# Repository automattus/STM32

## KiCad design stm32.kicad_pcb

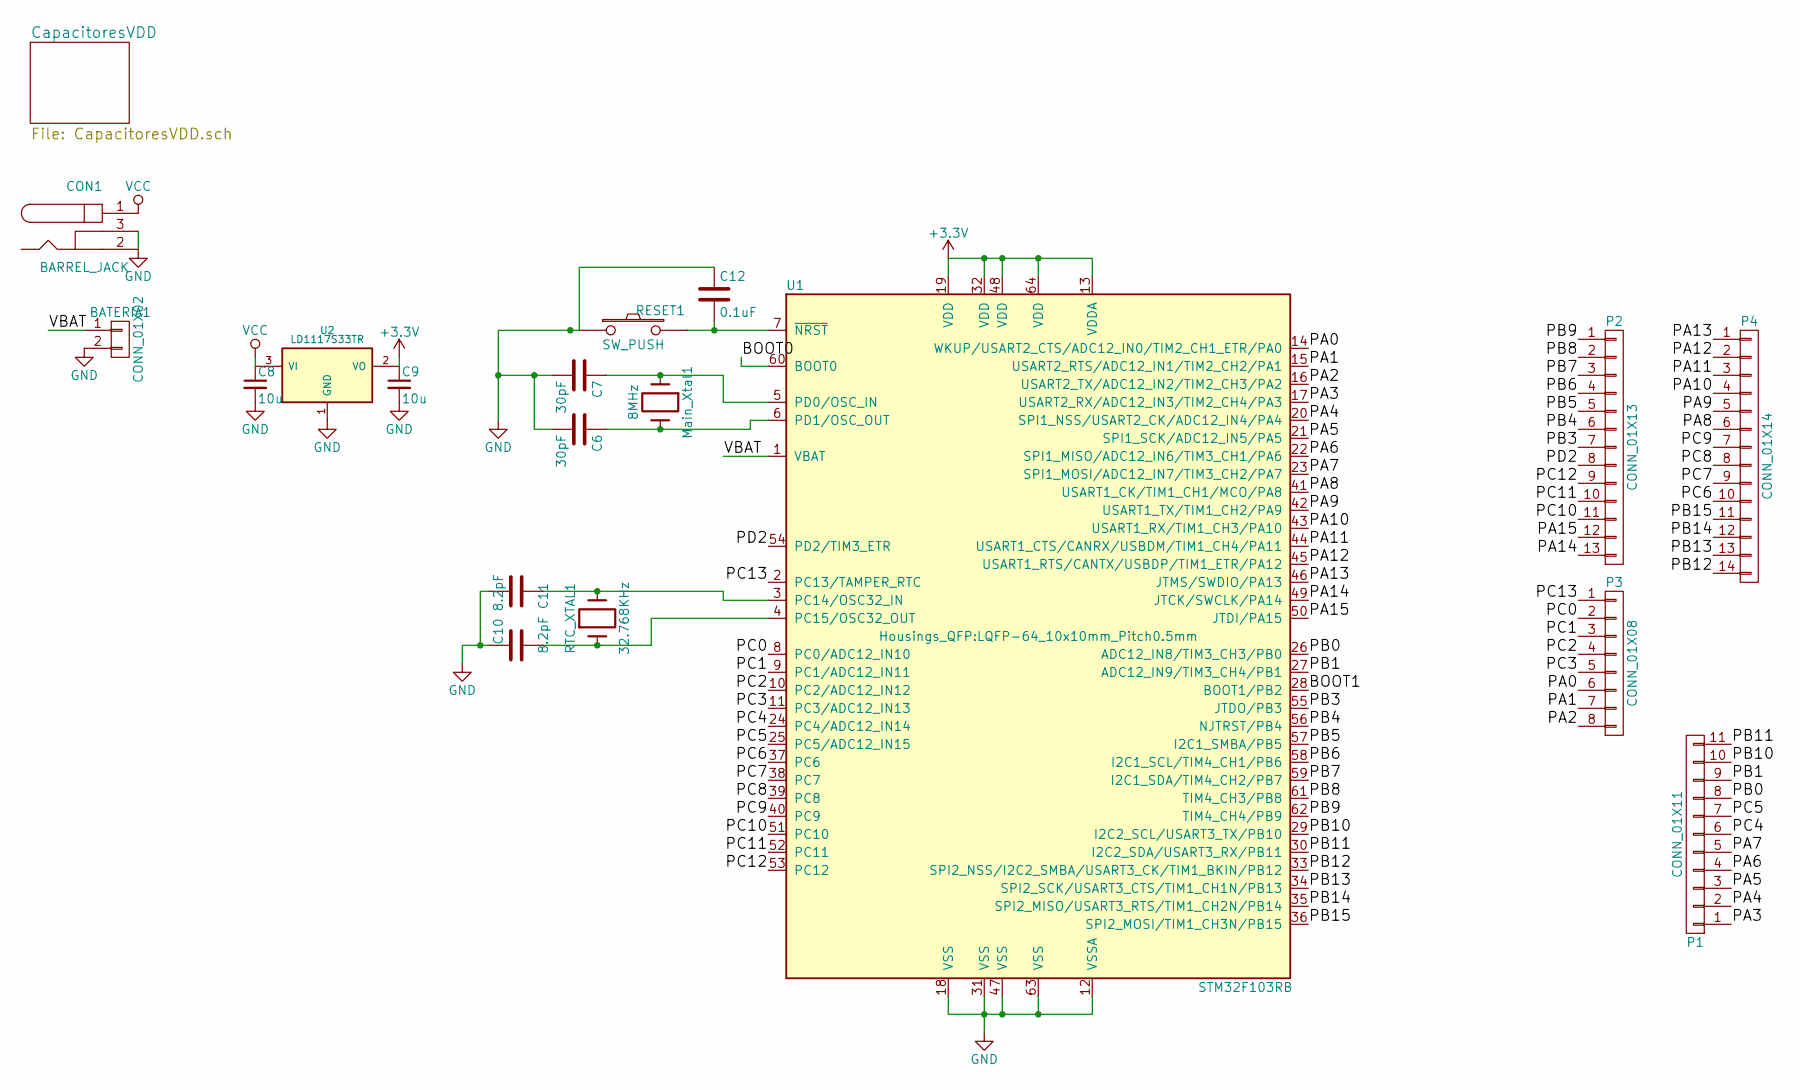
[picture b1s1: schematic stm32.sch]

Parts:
BATERIA1: CONN_01X02; bornier2
C6, C7: 30pF; C_0603_HandSoldering
C8, C9: 10u; C_0603_HandSoldering
C10, C11: 8.2pF; C_0603_HandSoldering
C12: 0.1uF; C_0603_HandSoldering
CON1: BARREL_JACK
Main_Xtal1: 8MHz; HC-18UV
P1: CONN_01X11; Pin_Header_Straight_1x11
P2: CONN_01X13; Pin_Header_Straight_1x13
P3: CONN_01X08; Pin_Header_Straight_1x08
P4: CONN_01X14; Pin_Header_Straight_1x14
RESET1: SW_PUSH; SW_PUSH_SMALL
RTC_XTAL1: 32.768KHz; Crystal_Round_Vertical_3mm
U1: STM32F103RB; LQFP-64_10x10mm_Pitch0.5mm
U2: LD1117S33TR; SOT-223

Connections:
+3V3: C9.1, U1.13 (VDDA), U1.19 (VDD), U1.32 (VDD), U1.48 (VDD), U1.64 (VDD), U2.2 (VO); also elsewhere on the board
/PA0: P3.6, U1.14 (WKUP/USART2_CTS/ADC12_IN0/TIM2_CH1_ETR/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)
/PA1: P3.7, U1.15 (USART2_RTS/ADC12_IN1/TIM2_CH2/PA1)
/PA2: P3.8, U1.16 (USART2_TX/ADC12_IN2/TIM2_CH3/PA2)
/PA3: P1.1, U1.17 (USART2_RX/ADC12_IN3/TIM2_CH4/PA3)
/PA4: P1.2, U1.20 (SPI1_NSS/USART2_CK/ADC12_IN4/PA4)
/PA5: P1.3, U1.21 (SPI1_SCK/ADC12_IN5/PA5)
/PA6: P1.4, U1.22 (SPI1_MISO/ADC12_IN6/TIM3_CH1/PA6)
/PA7: P1.5, U1.23 (SPI1_MOSI/ADC12_IN7/TIM3_CH2/PA7)
/PA8: P4.6, U1.41 (USART1_CK/TIM1_CH1/MCO/PA8)
/PA9: P4.5, U1.42 (USART1_TX/TIM1_CH2/PA9)
/PA10: P4.4, U1.43 (USART1_RX/TIM1_CH3/PA10)
/PA11: P4.3, U1.44 (USART1_CTS/CANRX/USBDM/TIM1_CH4/PA11)
/PA12: P4.2, U1.45 (USART1_RTS/CANTX/USBDP/TIM1_ETR/PA12)
/PA13: P4.1, U1.46 (JTMS/SWDIO/PA13)
/PA14: P2.13, U1.49 (JTCK/SWCLK/PA14)
/PA15: P2.12, U1.50 (JTDI/PA15)
/PB0: P1.8, U1.26 (ADC12_IN8/TIM3_CH3/PB0)
/PB1: P1.9, U1.27 (ADC12_IN9/TIM3_CH4/PB1)
/PB3: P2.7, U1.55 (JTDO/PB3)
/PB4: P2.6, U1.56 (NJTRST/PB4)
/PB5: P2.5, U1.57 (I2C1_SMBA/PB5)
/PB6: P2.4, U1.58 (I2C1_SCL/TIM4_CH1/PB6)
/PB7: P2.3, U1.59 (I2C1_SDA/TIM4_CH2/PB7)
/PB8: P2.2, U1.61 (TIM4_CH3/PB8)
/PB9: P2.1, U1.62 (TIM4_CH4/PB9)
/PB10: P1.10, U1.29 (I2C2_SCL/USART3_TX/PB10)
/PB11: P1.11, U1.30 (I2C2_SDA/USART3_RX/PB11)
/PB12: P4.14, U1.33 (SPI2_NSS/I2C2_SMBA/USART3_CK/TIM1_BKIN/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)
/PB13: P4.13, U1.34 (SPI2_SCK/USART3_CTS/TIM1_CH1N/PB13)
/PB14: P4.12, U1.35 (SPI2_MISO/USART3_RTS/TIM1_CH2N/PB14)
/PB15: P4.11, U1.36 (SPI2_MOSI/TIM1_CH3N/PB15)
/PC0: P3.2, U1.8 (PC0/ADC12_IN10)
/PC1: P3.3, U1.9 (PC1/ADC12_IN11)
/PC2: P3.4, U1.10 (PC2/ADC12_IN12)
/PC3: P3.5, U1.11 (PC3/ADC12_IN13)
/PC4: P1.6, U1.24 (PC4/ADC12_IN14)
/PC5: P1.7, U1.25 (PC5/ADC12_IN15)
/PC6: P4.10, U1.37 (PC6)
/PC7: P4.9, U1.38 (PC7)
/PC8: P4.8, U1.39 (PC8)
/PC9: P4.7, U1.40 (PC9)
/PC10: P2.11, U1.51 (PC10)
/PC11: P2.10, U1.52 (PC11)
/PC12: P2.9, U1.53 (PC12)
/PC13: P3.1, U1.2 (PC13/TAMPER_RTC)
/PD2: P2.8, U1.54 (PD2/TIM3_ETR)
/VBAT: BATERIA1.1, U1.1 (VBAT)
GND: BATERIA1.2, C6.2, C7.2, C8.2, C9.2, C10.1, C11.2, C12.1, CON1.2, CON1.3, RESET1.1, U1.12 (VSSA), U1.18 (VSS), U1.31 (VSS), U1.47 (VSS), U1.63 (VSS), U2.1 (GND); also elsewhere on the board
unnamed: C6.1, Main_Xtal1.2, U1.6 (PD1/OSC_OUT)
unnamed: C7.1, Main_Xtal1.1, U1.5 (PD0/OSC_IN)
unnamed: C10.2, RTC_XTAL1.1, U1.4 (PC15/OSC32_OUT)
unnamed: C11.1, RTC_XTAL1.2, U1.3 (PC14/OSC32_IN)
unnamed: C12.2, RESET1.2, U1.7 (~NRST)
VCC: C8.1, CON1.1, U2.3 (VI)

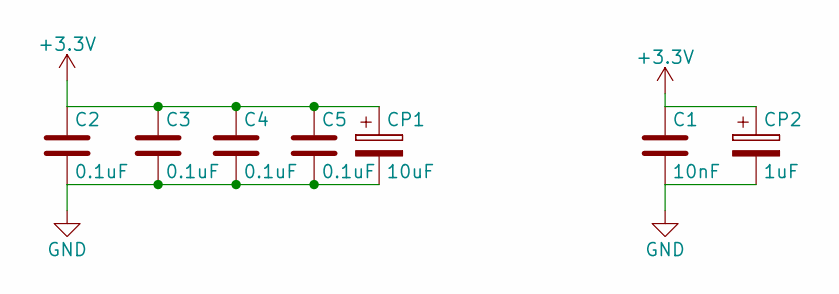
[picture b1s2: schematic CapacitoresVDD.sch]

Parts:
C1: 10nF; C_0603_HandSoldering
C2, C3, C4, C5: 0.1uF; C_0603_HandSoldering
CP1: 10uF; C_0603_HandSoldering
CP2: 1uF; C_0603_HandSoldering

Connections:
+3V3: C1.1, C2.1, C3.1, C4.1, C5.1, CP1.1, CP2.1; also elsewhere on the board
GND: C1.2, C2.2, C3.2, C4.2, C5.2, CP1.2, CP2.2; also elsewhere on the board

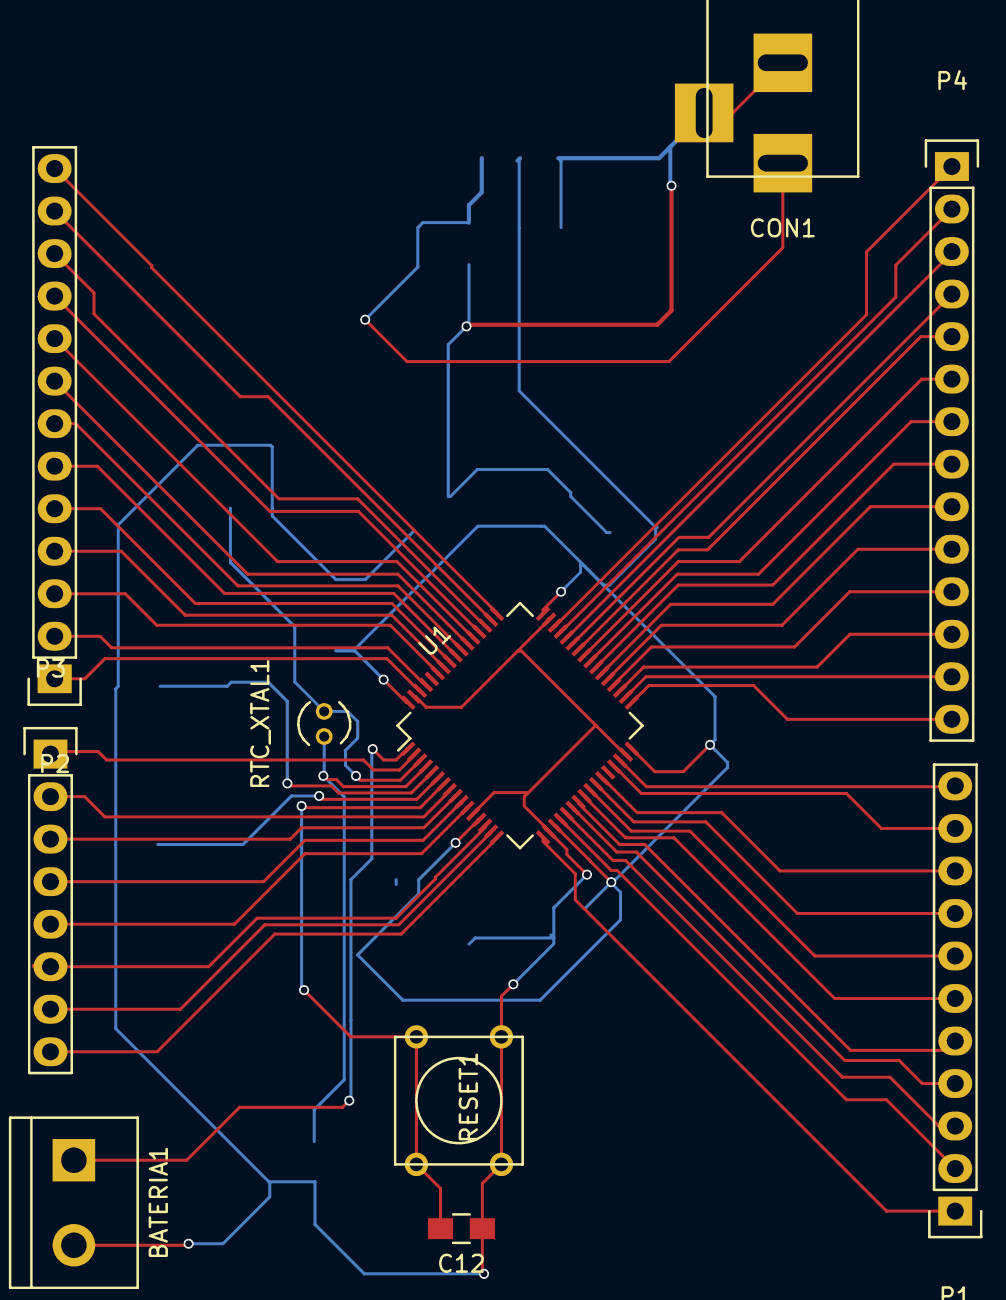
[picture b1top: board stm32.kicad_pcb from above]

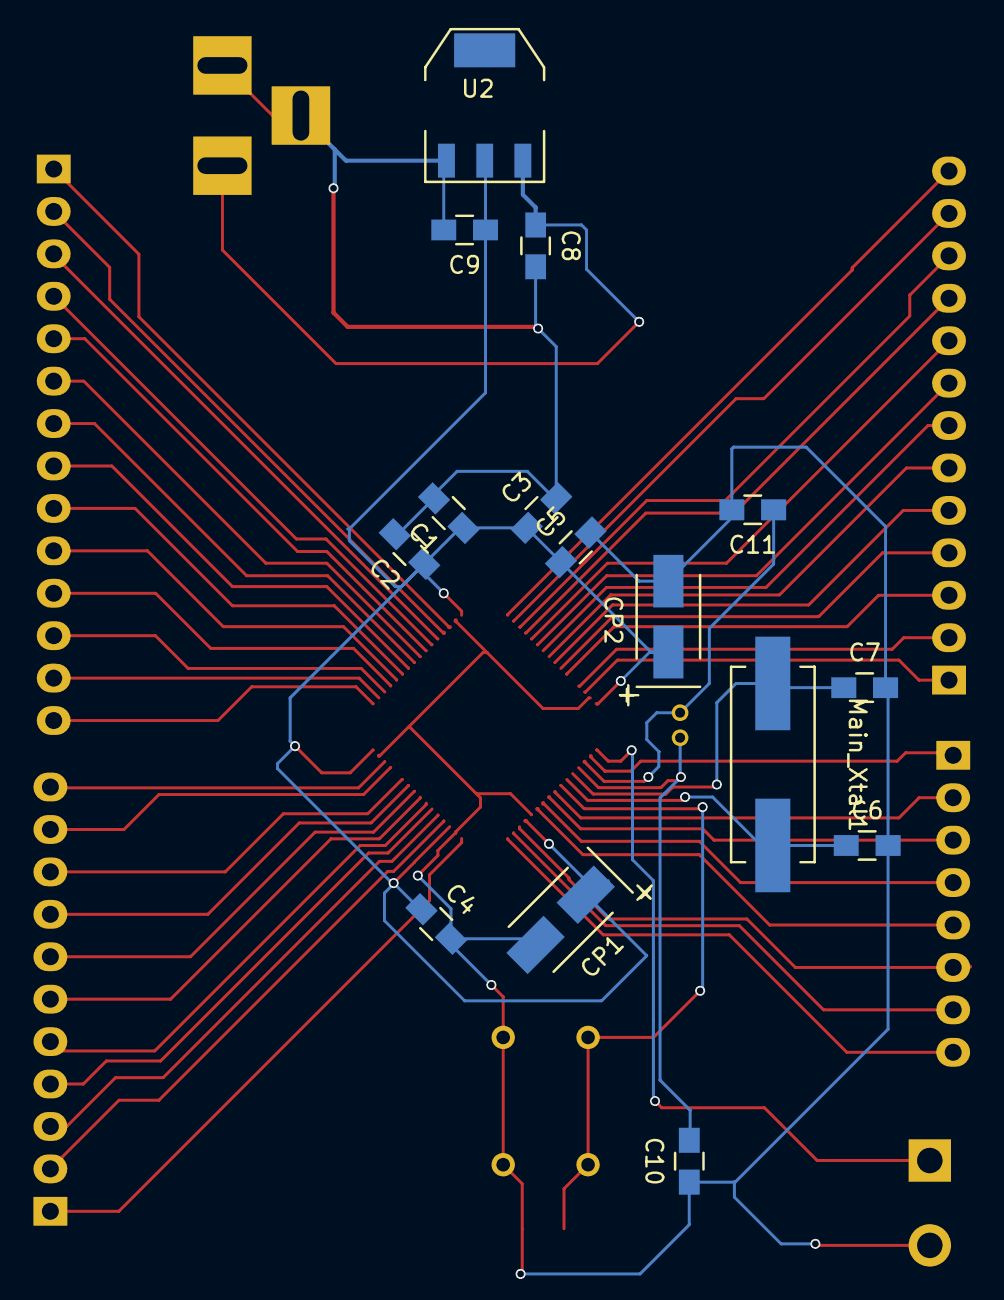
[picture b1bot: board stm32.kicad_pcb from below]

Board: 2 copper layers, 25 parts (15 on the bottom side), 55 nets.

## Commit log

2016-04-28 :boom::camel: Added .gitattributes & .gitignore files
2016-04-28 BREAKOUT PARA STM32
2016-04-30 ajustes
    corrigido a inversão do valor com referencia
    diminuido a largura da trilha.
    trocado componentes por smd
